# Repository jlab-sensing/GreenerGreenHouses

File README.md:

# JLab - Greener Greenhouses Sensing Project

This repository contains concurrent work for the Greener Greenhouses research project.

## Repository Contents

- **MSP430**
  
    Contains a general library for the [TI MSP430FR5969](https://www.ti.com/tool/MSP-EXP430FR5969?DCMP=mcugen&HQS=ep-mcu-msp-mcugen-mspblog-pf1-en) microcontroller to communicate with the [HDC2021](https://www.ti.com/product/HDC2021?utm_source=google&utm_medium=cpc&utm_campaign=asc-null-null-GPN_EN-cpc-pf-google-wwe&utm_content=HDC2021&ds_k=HDC2021&DCM=yes&gclid=Cj0KCQjwrfymBhCTARIsADXTabmBxpIyiHJQwz-0fqVoGLloWWmzIEXDT699dNn-ivyHtGXB0x-GpR8aAtybEALw_wcB&gclsrc=aw.ds) Temperature and Humidity Sensor.
  
- **PassiveLiFiTag**

    Includes schematic files for a prototype of the Passive LiFi IoT tag using the TI MSP430FR5969 microcontroller

- **RH_T_Replacement_Board**

    Contains .ino test harness and data storage files for HDC2021 sensor testing using Arduino. Also contains Eagle hardware files for the GGH RH/T replacement board
    
- **LoRa_BoosterPack_Registers**

    Contains register names and settings for ETSI CAT1 869MHz. 1.2Kbps, 2-GFSK, 25Khz channel spacing, ETSI EN 300 220 CAT1 setting with the [CC1125 LoRa module Boosterpack](https://www.ti.com/tool/BOOSTXL-CC1125). Register names and values exported from [SmartRFStudio v7.0](https://www.ti.com/tool/SMARTRFTM-STUDIO) for packet Tx/Rx.

- **BeagleBoneBlack**

    Contains source code for Beaglebone Black development, specifically work on SPI to LoRa boosterpack compatability, and ModbusLib test code for server/client side testing.

  ## To Do

  - [x] Create specific README file for each directory
  - [ ] file cleanup - remove defunct or unnecessary files
  - [ ] Update root README when new directories are created
  - [x] Standardize naming conventions for each directory
  - [x] License Project under MIT

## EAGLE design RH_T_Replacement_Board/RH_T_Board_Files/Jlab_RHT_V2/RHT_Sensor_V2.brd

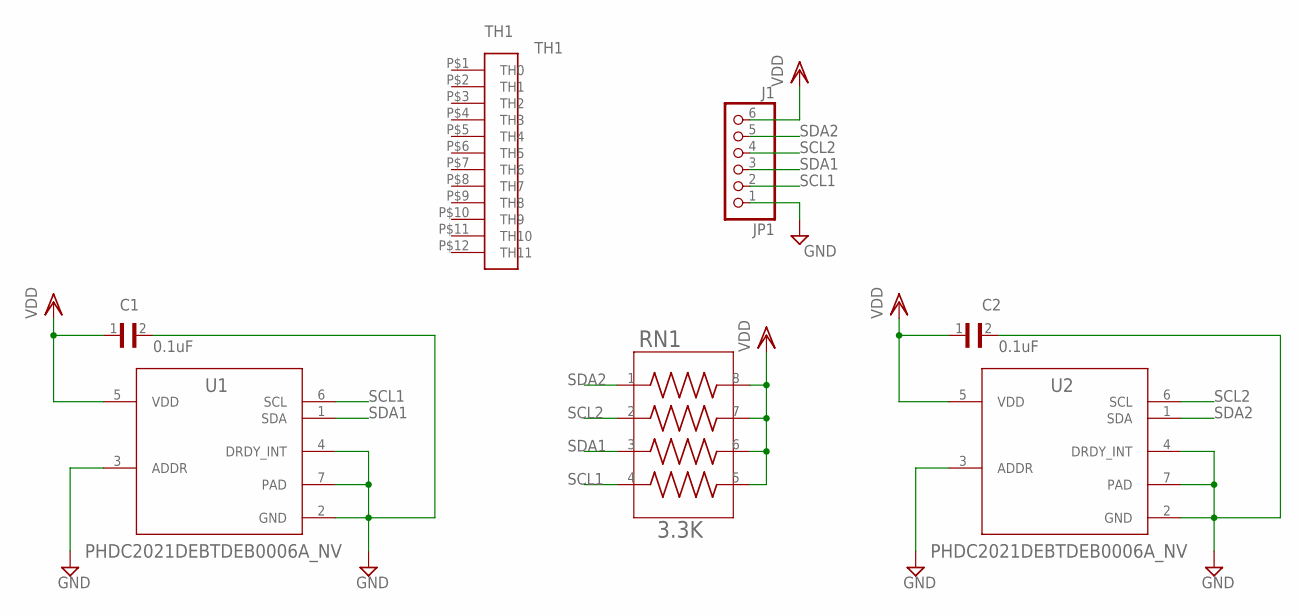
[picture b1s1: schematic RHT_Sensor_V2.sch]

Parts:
C1, C2: 0.1uF; CAPC2012X94N
JP1: J1; 1X06
RN1: 3.3K; RESCAF80P320X160X60-8N
TH1: TH1; 1MM_HEADER_01X12
U1, U2: PHDC2021DEBTDEB0006A_NV; DEB0006A_NV

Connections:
GND: C1.2, C2.2, JP1.1, U1.2 (GND), U1.3 (ADDR), U1.4 (DRDY_INT), U1.7 (PAD), U2.2 (GND), U2.3 (ADDR), U2.4 (DRDY_INT), U2.7 (PAD)
SCL1: JP1.2, RN1.4, U1.6 (SCL)
SCL2: JP1.4, RN1.2, U2.6 (SCL)
SDA1: JP1.3, RN1.3, U1.1 (SDA)
SDA2: JP1.5, RN1.1, U2.1 (SDA)
VDD: C1.1, C2.1, JP1.6, RN1.5, RN1.6, RN1.7, RN1.8, U1.5 (VDD), U2.5 (VDD)

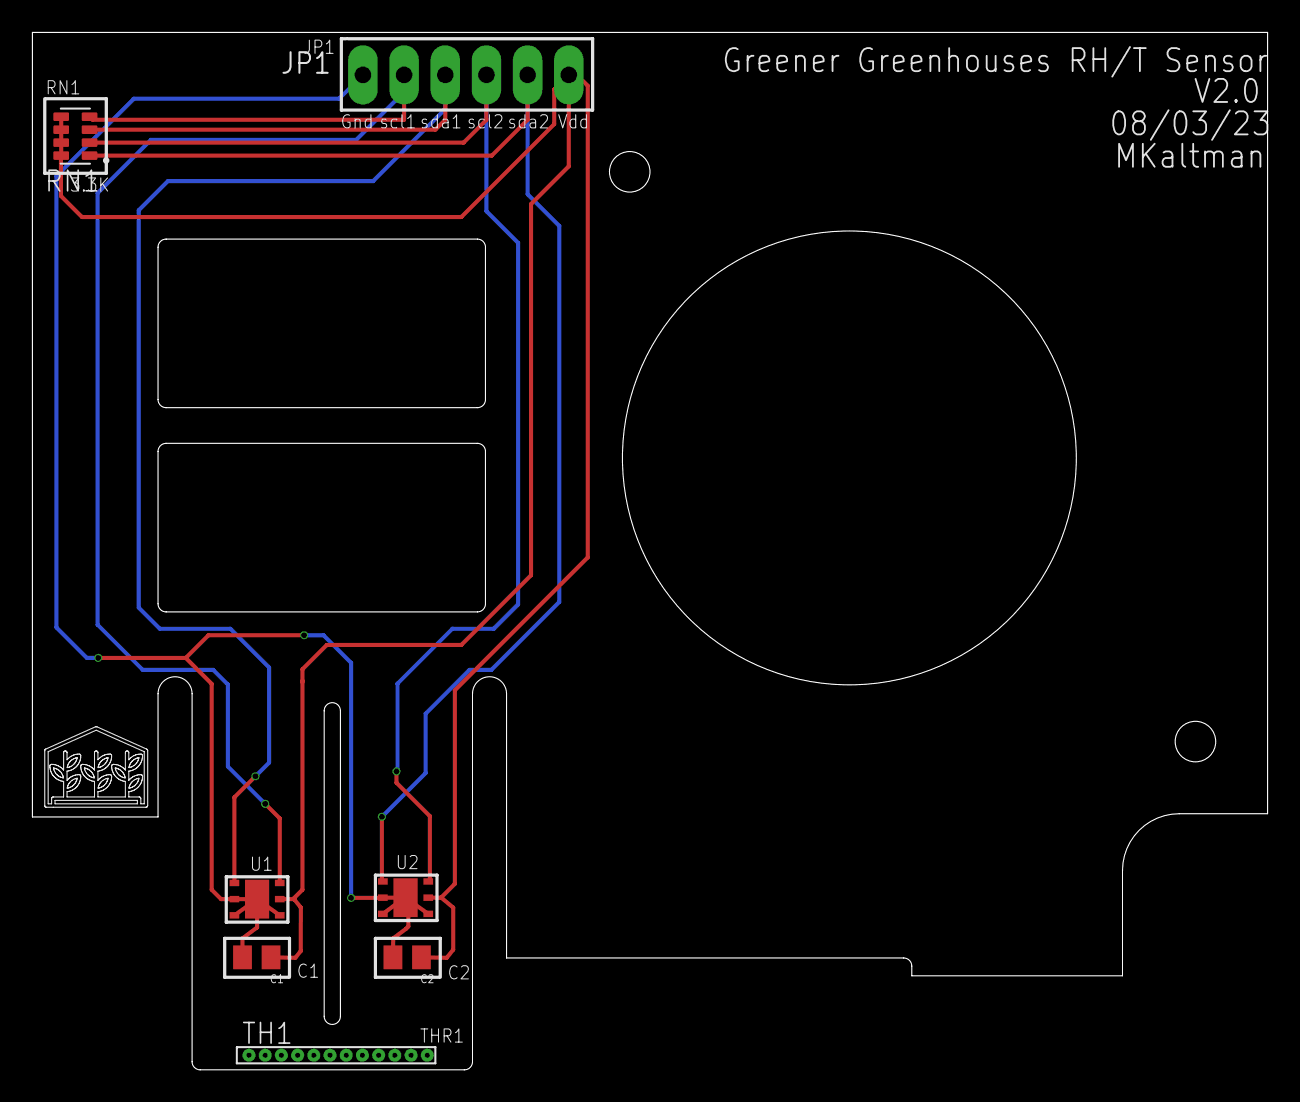
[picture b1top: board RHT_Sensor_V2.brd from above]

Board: 2 copper layers, 76.2 x 64.0 mm, 7 parts (0 on the bottom side), 6 nets.

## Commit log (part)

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2023-07-12 gitignore backups"
2023-07-12 PassiveLiFiTag empty schematic
2023-07-13 PassiveLiFi parts placed and library
2023-07-17 created replacement board folder for replacement board files
2023-07-17 added RH_T Test harness
2023-07-18 Added Matlab code for temp/humidity profile graph
2023-07-18 added RH/T arduino I2C Library
2023-07-18 started writing code for test harness, need to add sd card data reading portion
2023-07-18 Added text files for HVT data
2023-07-18 Created folder for HVT data files
2023-07-18 added text files for sd card to read/write to and SPI lib for communication
2023-07-19 HVT code ~should~ be done and ready to run
2023-07-24 added matlab code that compares power consumption of 3 sensors
2023-07-25 edit to supply current to one of the sensors
2023-07-25 edits to voltages
2023-07-27 initial test code complete. need to add softwire functionality to poll both I2C sensors
2023-07-27 Initial (backyard) RH/T test raw data added
2023-07-28 added sketch of digital I2C attempt
2023-08-14 adding MSP430 sensor sketch, Matt's github does not work
2023-08-16 Working Temperature polling code for MSP430 with CCS
2023-08-16 whole i2c project
2023-08-16 Created project with headers for i2c and hdc2021
2023-08-17 Created CCS project for communication between MSP430FR5969 and HDC2021 RH/T Sensor
2023-08-17 removed redundant and unecessary ccs project directories
2023-08-17 removed unneccesary read/write commands as they will be abstracted through functions utilizing MSP430_I2C
2023-08-17 Removed unnnecessary #defines and added function descriptions
2023-08-17 Added i2c header and beginning i2c.c file, removed master/slave terminology
2023-08-17 Configuration functions for HDC2080 done
2023-08-17 Rough draft of I2C ready to integrate and test
2023-08-17 main.c will poll for sensors device id and manufacturer id and store in memory
2023-08-17 Added extern variables to main for proper Tx and Rx behavior
2023-08-17 Matt check ReceiveBuffer
2023-08-17 small I2C lib adjustment
2023-08-17 update on buffers
2023-08-17 register transceiving is done in sensor library
2023-08-17 sensor reset written
2023-08-17 Created README skeleton and cleaned up functions
2023-08-17 removed .txt readme to replace with a .md
2023-08-18 added comments to .c library file
2023-08-18 reverting arduino test harness back to original code after accidental delete
2023-08-18 created README for root directory
2023-08-18 Create README.md for PassiveLiFiTag
2023-08-18 Updated root README.md
2023-08-18 Removed old dummy data directory
2023-08-18 Create LICENSE for the repository
2023-08-21 Removed extern variable from HDC2021 library and main.c
2023-08-21 UART example added to repo
2023-08-21 Added UART lib skeleton and uart example to correct folder
2023-08-21 crude rendition of UART library finished, still have to use different clock and test
2023-08-21 added UART libraries to new project
2023-08-21 most recent work
2023-08-21 moved UART library back to I2c project, deleted UART project
2023-08-21 remove uart main
2023-08-22 more work debugging, havent gotten it to work yet
2023-08-22 added TI MSP430 Driver Library
2023-08-22 add TI proprietary UART driver attempt (DOES NOT WORK EITHER)
2023-08-23 added headers for raw sensor readings, will be used to send over LoRa and avoid FP operations on MSP
2023-08-23 removed UART library files because they are in other CCS project
2023-08-23 added offset adjust functions for temp and humidity as well as functions that return raw sensor reading in uint8_t format
2023-08-23 BBB test files
2023-08-23 UART lib finally works, issue was misplaced or-assign symbol
2023-08-23 Changed I2C clock operation from 16MHz -> 8MHz
2023-08-23 added more test files from the successful SPI BME280 device ID read test
2023-08-23 reorganized
2023-08-23 lora registers from smartrf studio 7
2023-08-23 LoRa test read/write and burst defines
2023-08-24 attempted to interconnect UART with hdc2021 for data printing
2023-08-24 expanded sensor functions by adding 2 functions that enable and disable the sensor heating element
2023-08-24 need to fix timer declarations
2023-08-24 UART comms with sensor now work
2023-08-24 added humidity measurements as well
2023-08-24 added code comments, slight issue with sensor? temp and humidity dont change when continuously polling, but when resetting value changes first measurement and then doesnt change anymore after continu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
2023-08-24 Update root README
2023-08-25 reorganized and added config-pin scripts
2023-08-25 Added readme
2023-08-25 updated readme with attribution
2023-08-28 work on UART, attempting to implement circular buffer as a more efficient method of parsing buffers for transmission
2023-08-28 UART driver now works with circular buffer (with small delay between char transmissions)
2023-08-28 added comments
2023-08-28 CC1125 demo not building for BBB
2023-08-28 Modification based on SWRC253E for CC1125, compiles for BBB
2023-08-28 comments and TX buffer interrupt addition
2023-08-28 changes in main example
2023-08-28 smartrf studio 7 register values for the boosterpack, and LoRa boosterpack SPI test (register read/write/read) for BBB
2023-08-29 blank readme and reorganized config-pin scripts
2023-08-29 readme for BBB LoRa boosterpack folder
2023-08-29 wiring diagram
2023-08-29 readme updated to reflect config-pin reorganization
2023-08-29 libmodbus test files
2023-08-30 UART putc()/puts() working for terminal output (9600, 8-N-1)
2023-08-30 master and slave test libmodbus
2023-08-30 BBB modbus slave incorrect reply or malformed output
2023-08-30 updates to readme in this directory for higher accuracy on contents
2023-08-30 added fun message
2023-08-31 Not completely working yet
2023-09-01 device number function
2023-09-01 edits, doesnt work
2023-09-01 SPI working on MSP430 to communicate with LoRa boosterpack
2023-09-01 Uart working in conjunction with LoRa SPI
2023-09-01 SPI UART test formatting and code comments, removed UART_example and LaunchPad_trx_demo directories due to old, outdated, and non functioning code
2023-09-01 renamed spi uart directory
2023-09-01 BBB libmodbus master command and slave reply ok
2023-09-01 reorganized libmodbus old test files and added readme (no image)
2023-09-01 LoRa Module Communication almost complete, register initializations tested
2023-09-05 Added uart lib for easier client use, only has putc() and puts()
2023-09-05 created initSpi() in main.c so main function is cleaner
2023-09-05 Created better looking/clearer terminal test harness
2023-09-05 added basic Rx test, will be tested later today
2023-09-05 LoRa boosterpack registers are the same for packet txrx
2023-09-05 fixed register name to 112X
2023-09-05 Communication between LoRa modules established
2023-09-05 added allSettings (don't access .data), modified main (untested) for RX
2023-09-06 comments and code formatting
2023-09-06 removed copy of cc1125 directory and added readme to final SPI attempt
2023-09-06 adding Tx code
2023-09-06 moved InitUart to uart library instead of temp main
2023-09-06 fixed naming convention
2023-09-06 actually fixed issue
2023-09-06 Tim taking over Tx
2023-09-06 added new directory for board files
2023-09-06 cleaning up files for board data/sch
2023-09-06 removed empty/unneccessary directory
2023-09-06 bbb rx, only 1 byte rx?
2023-09-07 got RF transmission to work, no CRC error anymore by setting fixed message length in RF register configurations
2023-09-07 fixed last commit to have no errors/warnings
2023-09-07 MSP430 Tx working 100%
2023-09-07 attempting to integrate RH/T
2023-09-07 added switch statemnet for easier switching between TX and RX testing mode
2023-09-07 HDC2080 working with uart printing, need to move to LoRa
2023-09-07 removed unecessary comments, and added test case selector
2023-09-08 Moved SPI to EUSCIA1 from EUSCIB0
2023-09-08 ready for packet creation function
2023-09-08 added packet creator function in cc112x_spi library
2023-09-09 BBB tx 'test' (fixed 4 byte) to smartrf OK, still rx fifo error on BBB
2023-09-11 BBB test code for monitoring MARCSTATE register correctly increments RX FIFO length
2023-09-11 Finished packet creation and MSP->BBB comms, need to clean up code
2023-09-11 rxlogger for BBB to write temp/humidity data from MSP430 to file
2023-09-11 put all packet creation lines into unified function
2023-09-11 cleaning up main.c and implementing power saving changes
2023-09-11 finished cleaning up/commenting main_tester.c, need to add LPM in intterupt and while loop
2023-09-11 rxlogger with lora, logging, and modbus reply (modbus untested). may segfault if MAP_SIZE_xxxx are set too low
2023-09-12 implemented LowPowerMode3. Now wakes up to take measurement and goes back to sleep
2023-09-12 formatting and function comments, added packet unpacker function if necessary to unpack packets
2023-09-12 added bit masking to constructor, timers ARE MESSED UP
2023-09-12 Updated packet parser to calculate temperature and humidity based on the upper 14 bits
2023-09-12 added csv logging based on unix time
2023-09-13 removed destroy packet, not necessary :(
2023-09-13 changed bit shift in packetCreate to discord last 2 bits and include first 2 bits instead
2023-09-13 nonblocking modbus receive (build libmodbus from source and adjust indication timeout), basic modbus map modification
2023-09-13 added define to change packet length easily
2023-09-13 equalizing local and remote README version
2023-09-13 LPM3 working with sensor Tx
2023-09-14 Created github onboarding
2023-09-14 renamed LoRa test harness file
2023-09-14 removed defunct Booster_Pack_LoRa_SPI, to remove confusion and is unecessary
2023-09-14 added folder for images and assets
2023-09-14 change to readme :
2023-09-14 Update README.md, from different computer
2023-09-15 fixed parameter order for modbus_init to match parameter order of modbus_mapping_new
2023-09-15 rxlogger fixed modbus_mapping_new and modbus_init parameter order
2023-09-15 removed hal_defs and hal_types with stdint
2023-09-15 rxlogger readme
2023-09-17 added wiring image to github to display in readme
2023-09-18 readmes for BBB
2023-09-18 minor readme changes, added comments to some parts of the code, and return values for init functions
2023-09-18 renamed executable to rxlogger
2023-09-18 readme clarifications on debian libmodbus prebuilt incompatibility
2023-09-19 BBB setup readme, and rxlogger readme update
2023-09-21 readme LiFi control
2023-09-21 readme formatting fixes
2023-09-21 readme libmodbus
2023-09-25 mac USB fix
2023-10-02 added eth0 alias fix instructions to prevent wlan0 default route clobbering
2023-10-02 fixed links, recommend eth0 alias method
2023-10-11 gpio testing for maximizing frequency on the main processor
2023-10-12 direct memory map access to gpio registers results in 360 ns period. faster speeds must be done on PRU
2023-10-12 extended led direct memory map method to do two pins (same chip) alternating
2023-10-13 readme note on disabling strict host key checking
2023-10-13 moved GPIO_test to BBB, updated rxlogger wiring for SYS_5V, cleaned up rxlogger main globals inits prints
2023-10-14 added expected routing table to readme
2023-10-14 GPIO_test brief
2023-10-16 moved modbus map printing to only trigger if a packet was received, also added some sample data received from the MSP
2023-10-19 pru example with 5ns pin access time
2023-10-24 upchirp example
2023-10-25 upchirp with log(?) shifting exhibits significant ringing
2023-10-31 ecr! 1 command to re-enable DC11 response
2023-11-01 added crontab instructions for automation
2023-11-02 manual bootup sequence, which does not solve the calibration issue
2023-11-07 c89 --> c99, 6 byte packet format, disabled debug print messages in main loop
2023-11-07 updated to 6 byte packet format
2024-01-12 Added (incredibly) simple code for linear chirps on EttusN200 USRP
2024-01-17 re-added uart files, idk why they were removed
2024-01-18 Ported relevent FR5969 code to FR994
2024-01-25 Started Hardware design for LiFi Receiver
2024-01-29 Added some small peripherals and voltage supplies/decoupling caps
2024-01-29 Continuing to update Hardware Design
2024-01-30 hopefully fixed git errors
2024-02-07 updating changes
2024-02-07 added Updates

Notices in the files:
parts and their libraries:
COPYRIGHT: Copyright (C) 2023 Ultra Librarian. All rights reserved.
